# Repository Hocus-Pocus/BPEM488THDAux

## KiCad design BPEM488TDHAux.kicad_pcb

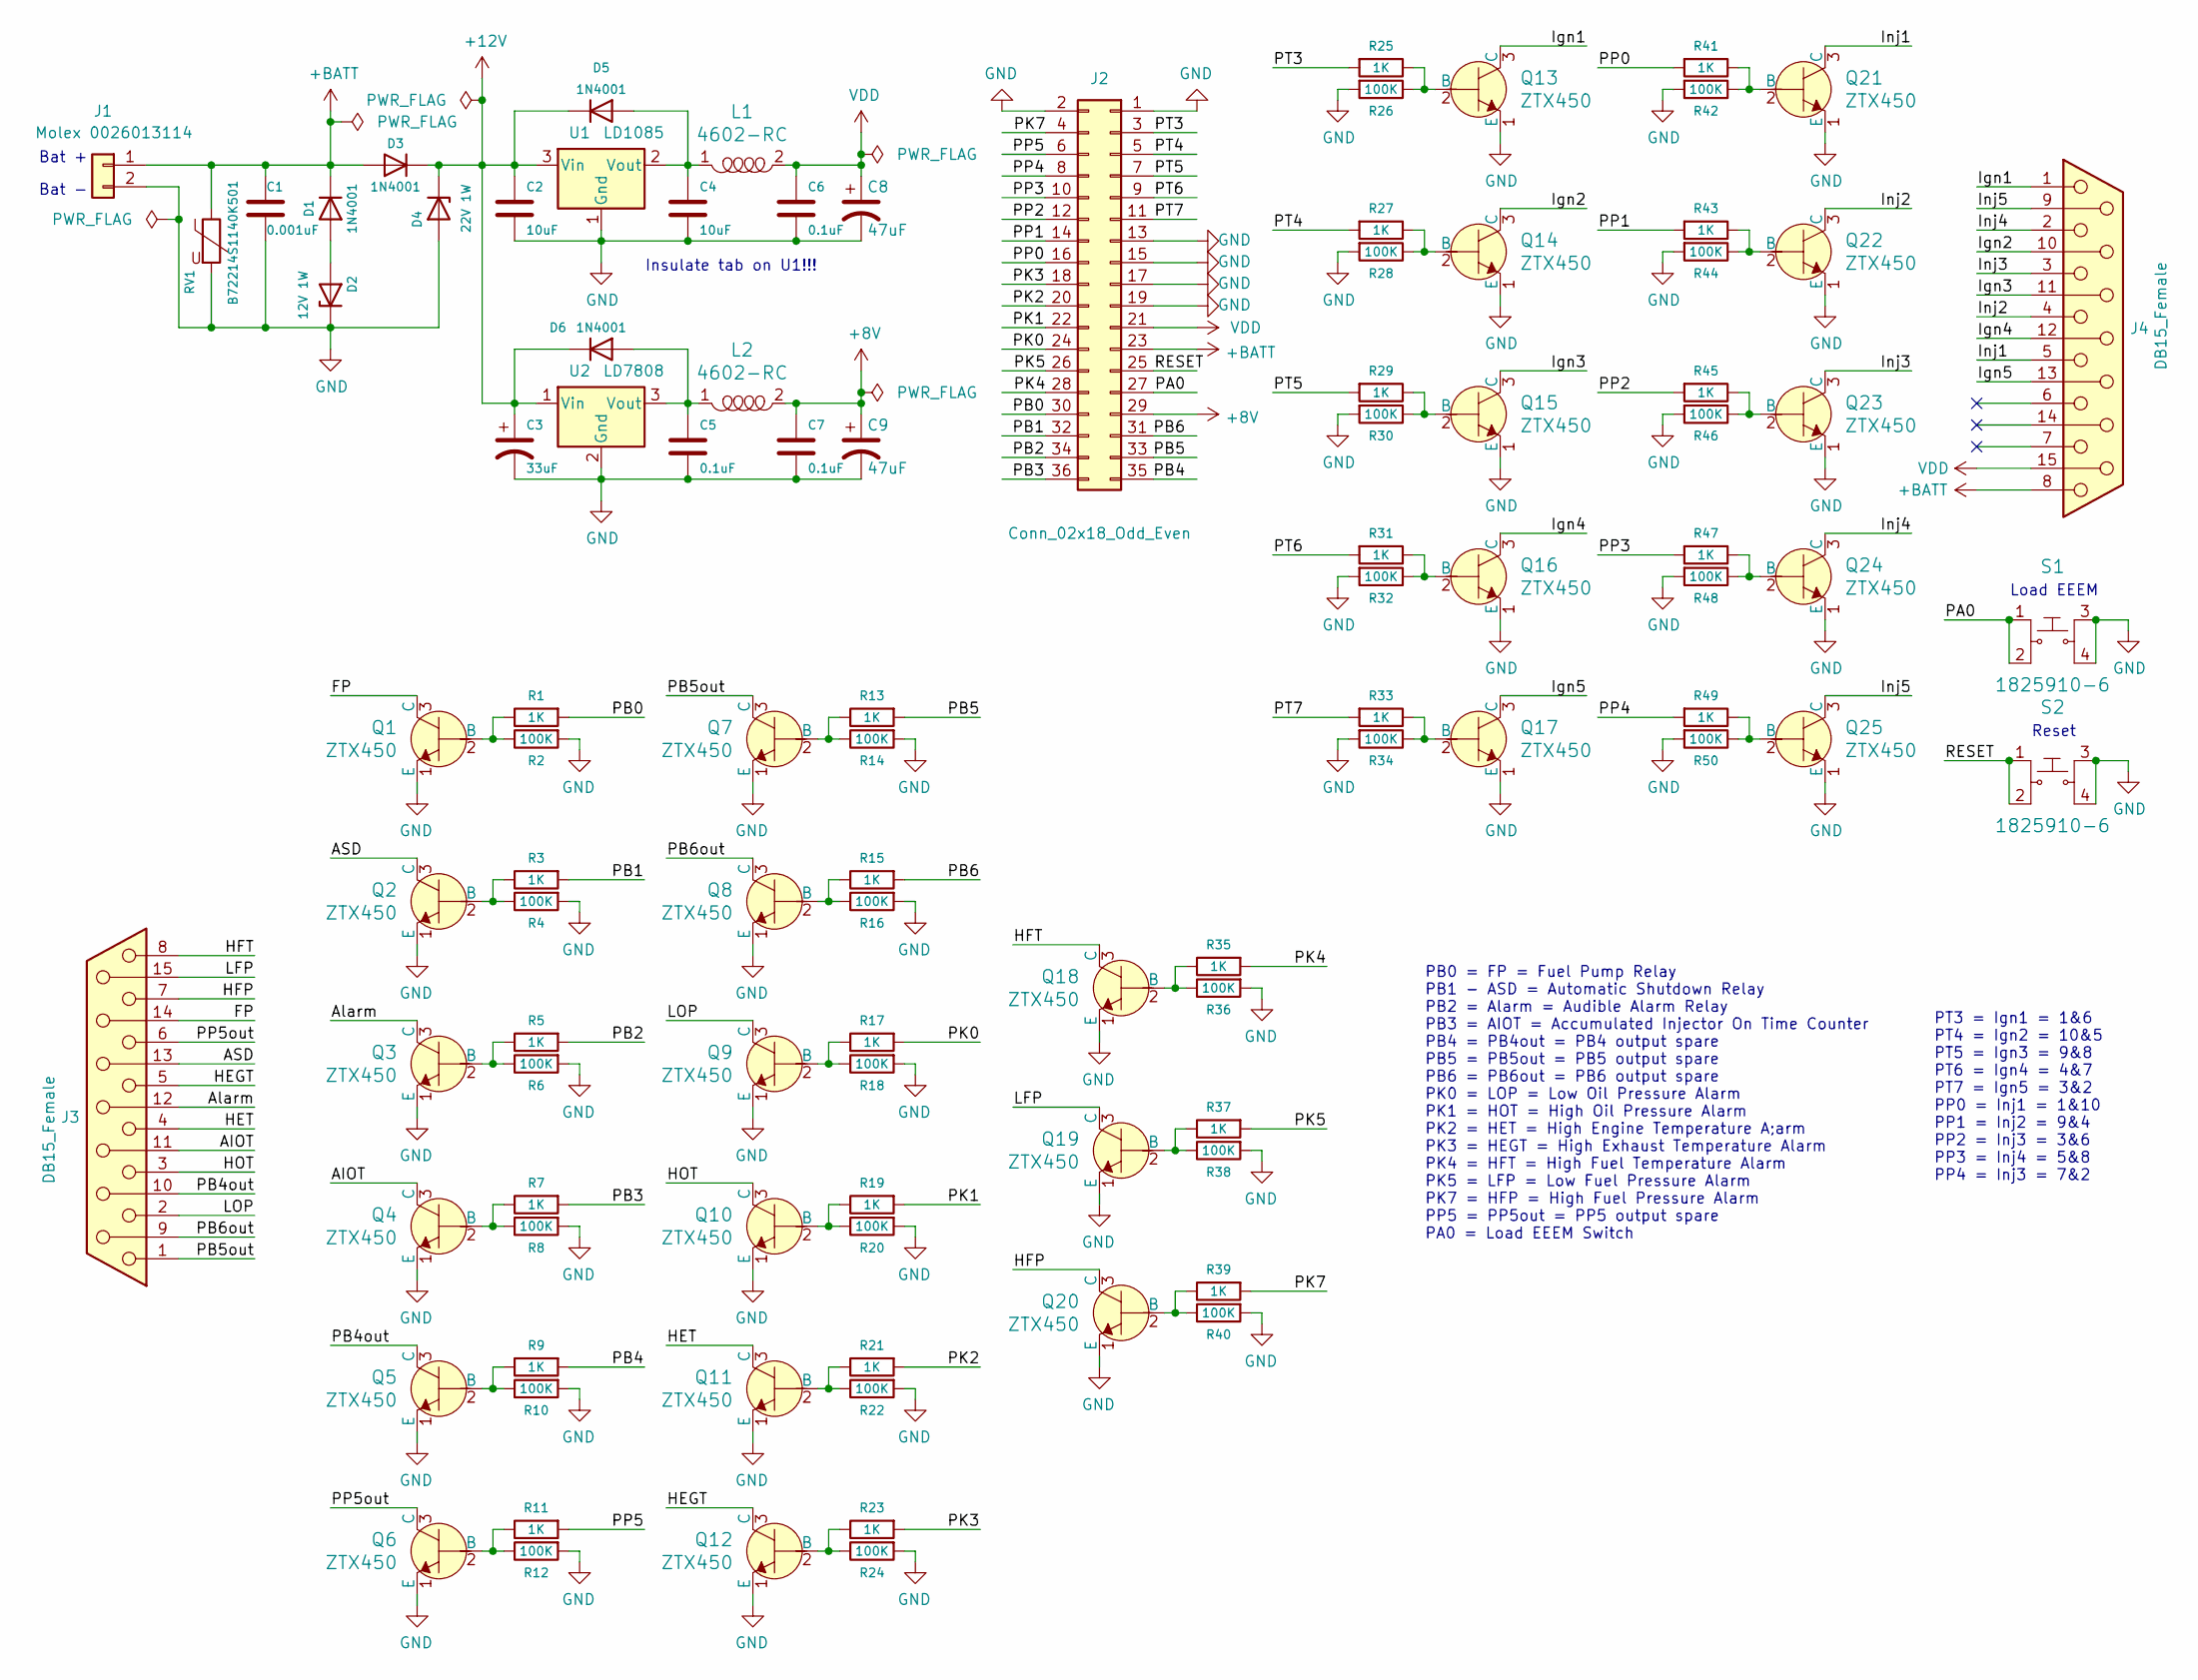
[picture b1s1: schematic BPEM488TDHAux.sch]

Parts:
C1: 0.001uF; C_Disc_D3.8mm_W2.6mm_P2.50mm; Digikey 399-13913-2-ND
C2, C4: 10uF; C_Disc_D5.0mm_W2.5mm_P2.50mm; Digikey 399-13950-ND
C3: 33uF; CP_Radial_Tantal_D8.0mm_P5.00mm; Digikey 399-3591-ND
C5, C6, C7: 0.1uF; C_Disc_D5.0mm_W2.5mm_P2.50mm; Digikey 399-4264-ND
C8, C9: 47uF; CP_Radial_Tantal_D8.0mm_P5.00mm; Digikey 399-3596-ND
D1, D3, D5, D6: 1N4001; D_DO-41_SOD81_P7.62mm_Horizontal; Digikey 1N4001DICT-ND
D2: 12V 1W; D_DO-41_SOD81_P7.62mm_Horizontal; Digikey 1727-3635-2-ND
D4: 22V 1W; D_DO-41_SOD81_P7.62mm_Horizontal; Digikey MAZ222000GTR-ND
J1: Molex 0026013114; Molex_Mini-Fit_Jr_5569-02A2_2x01_P4.20mm_Horizontal; Digikey WM14505-ND
J2: Conn_02x18_Odd_Even; PinSocket_2x18_P2.54mm_Vertical
J3, J4: DB15_Female; DSUB-15_Female_Horizontal_P2.77x2.84mm_EdgePinOffset7.70mm_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; Digikey A32123-ND
L1, L2: 4602-RC; L_Axial_L16.0mm_D6.3mm_P25.40mm_Horizontal_Fastron_VHBCC; Digikey 4602-RC-ND
Q1, Q2, Q3, Q4, Q5, Q6, Q7, Q8, Q9, Q10, Q11, Q12, Q13, Q14, Q15, Q16, Q17, Q18, Q19, Q20, Q21, Q22, Q23, Q24, Q25: ZTX450; TO-92-3; MPN ZTX450; Digi-Key_PN ZTX450-ND
R1, R3, R5, R7, R9, R11, R13, R15, R17, R19, R21, R23, R25, R27, R29, R31, R33, R35, R37, R39, R41, R43, R45, R47, R49: 1K; R_Axial_DIN0207_L6.3mm_D2.5mm_P10.16mm_Horizontal; Digikey 1.00KXBK-ND
R2, R4, R6, R8, R10, R12, R14, R16, R18, R20, R22, R24, R26, R28, R30, R32, R34, R36, R38, R40, R42, R44, R46, R48, R50: 100K; R_Axial_DIN0207_L6.3mm_D2.5mm_P10.16mm_Horizontal; Digikey 100KXBK-ND
RV1: B72214S1140K501; RV_Disc_D15.5mm_W3.9mm_P7.5mm; Digikey 495-2057-ND
S1, S2: 1825910-6; Switch_Tactile_THT_6x6mm; MPN 1825910-6; Digi-Key_PN 450-1650-ND
U1: LD1085; TO-220F-3_Horizontal_TabDown; Digikey 497-3436-5-ND
U2: LD7808; TO-220F-3_Horizontal_TabDown; Digike 497-1446-5-ND

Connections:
+8V: C7.1, C9.1, J2.29, L2.2
+12V: C2.1, C3.1, D3.1 (K), D4.1 (K), D5.1 (K), D6.1 (K), U1.3 (Vin), U2.1 (Vin)
+BATT: C1.1, D1.1 (K), D3.2 (A), J1.1, J2.23, J4.8, RV1.1
/AIOT: J3.11 (P111), Q4.3 (C)
/ASD: J3.13, Q2.3 (C)
/Alarm: J3.12, Q3.3 (C)
/FP: J3.14, Q1.3 (C)
/HEGT: J3.5, Q12.3 (C)
/HET: J3.4, Q11.3 (C)
/HFP: J3.7, Q20.3 (C)
/HFT: J3.8, Q18.3 (C)
/HOT: J3.3, Q10.3 (C)
/Ign1: J4.1, Q13.3 (C)
/Ign2: J4.10, Q14.3 (C)
/Ign3: J4.11 (P111), Q15.3 (C)
/Ign4: J4.12, Q16.3 (C)
/Ign5: J4.13, Q17.3 (C)
/Inj1: J4.5, Q21.3 (C)
/Inj2: J4.4, Q22.3 (C)
/Inj3: J4.3, Q23.3 (C)
/Inj4: J4.2, Q24.3 (C)
/Inj5: J4.9, Q25.3 (C)
/LFP: J3.15, Q19.3 (C)
/LOP: J3.2, Q9.3 (C)
/PA0: J2.27, S1.1, S1.2
/PB0: J2.30, R1.2
/PB1: J2.32, R3.2
/PB2: J2.34, R5.2
/PB3: J2.36, R7.2
/PB4: J2.35, R9.2
/PB4out: J3.10, Q5.3 (C)
/PB5: J2.33, R13.2
/PB5out: J3.1, Q7.3 (C)
/PB6: J2.31, R15.2
/PB6out: J3.9, Q8.3 (C)
/PK0: J2.24, R17.2
/PK1: J2.22, R19.2
/PK2: J2.20, R21.2
/PK3: J2.18, R23.2
/PK4: J2.28, R35.2
/PK5: J2.26, R37.2
/PK7: J2.4, R39.2
/PP0: J2.16, R41.2
/PP1: J2.14, R43.2
/PP2: J2.12, R45.2
/PP3: J2.10, R47.2
/PP4: J2.8, R49.2
/PP5: J2.6, R11.2
/PP5out: J3.6, Q6.3 (C)
/PT3: J2.3, R25.2
/PT4: J2.5, R27.2
/PT5: J2.7, R29.2
/PT6: J2.9, R31.2
/PT7: J2.11, R33.2
/RESET: J2.25, S2.1, S2.2
GND: C1.2, C2.2, C3.2, C4.2, C5.2, C6.2, C7.2, C8.2, C9.2, D2.1 (K), D4.2 (A), J1.2, J2.1, J2.2, J2.13, J2.15, J2.17, J2.19, Q1.1 (E), Q2.1 (E), Q3.1 (E), Q4.1 (E), Q5.1 (E), Q6.1 (E), Q7.1 (E), Q8.1 (E), Q9.1 (E), Q10.1 (E), Q11.1 (E), Q12.1 (E), Q13.1 (E), Q14.1 (E), Q15.1 (E), Q16.1 (E), Q17.1 (E), Q18.1 (E), Q19.1 (E), Q20.1 (E), Q21.1 (E), Q22.1 (E), Q23.1 (E), Q24.1 (E), Q25.1 (E), R2.2, R4.2, R6.2, R8.2, R10.2, R12.2, R14.2, R16.2, R18.2, R20.2, R22.2, R24.2, R26.2, R28.2, R30.2, R32.2, R34.2, R36.2, R38.2, R40.2, R42.2, R44.2, R46.2, R48.2, R50.2, RV1.2, S1.3, S1.4, S2.3, S2.4, U1.1 (Gnd), U2.2 (Gnd)
unnamed: C4.1, D5.2 (A), L1.1, U1.2 (Vout)
unnamed: C5.1, D6.2 (A), L2.1, U2.3 (Vout)
unnamed: D1.2 (A), D2.2 (A)
unnamed: Q1.2 (B), R1.1, R2.1
unnamed: Q2.2 (B), R3.1, R4.1
unnamed: Q3.2 (B), R5.1, R6.1
unnamed: Q4.2 (B), R7.1, R8.1
unnamed: Q5.2 (B), R9.1, R10.1
unnamed: Q6.2 (B), R11.1, R12.1
unnamed: Q7.2 (B), R13.1, R14.1
unnamed: Q8.2 (B), R15.1, R16.1
unnamed: Q9.2 (B), R17.1, R18.1
unnamed: Q10.2 (B), R19.1, R20.1
unnamed: Q11.2 (B), R21.1, R22.1
unnamed: Q12.2 (B), R23.1, R24.1
unnamed: Q13.2 (B), R25.1, R26.1
unnamed: Q14.2 (B), R27.1, R28.1
unnamed: Q15.2 (B), R29.1, R30.1
unnamed: Q16.2 (B), R31.1, R32.1
unnamed: Q17.2 (B), R33.1, R34.1
unnamed: Q18.2 (B), R35.1, R36.1
unnamed: Q19.2 (B), R37.1, R38.1
unnamed: Q20.2 (B), R39.1, R40.1
unnamed: Q21.2 (B), R41.1, R42.1
unnamed: Q22.2 (B), R43.1, R44.1
unnamed: Q23.2 (B), R45.1, R46.1
unnamed: Q24.2 (B), R47.1, R48.1
unnamed: Q25.2 (B), R49.1, R50.1
VDD: C6.1, C8.1, J2.21, J4.15, L1.2

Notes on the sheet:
Load EEEM
Reset
Bat -
Bat +
PB0 = FP = Fuel Pump Relay PB1 - ASD = Automatic Shutdown Relay PB2 = Alarm = Audible Alarm Relay PB3 = AIOT = Accumulated Injector On Time Counter PB4 = PB4out = PB4 output spare PB5 = PB5out = PB5 output spare PB6 = PB6out = PB6 output spare PK0 = LOP = Low Oil Pressure Alarm PK1 = HOT = High Oil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
PT3 = Ign1 = 1&6 PT4 = Ign2 = 10&5 PT5 = Ign3 = 9&8 PT6 = Ign4 = 4&7 PT7 = Ign5 = 3&2 PP0 = Inj1 = 1&10 PP1 = Inj2 = 9&4 PP2 = Inj3 = 3&6 PP3 = Inj4 = 5&8 PP4 = Inj3 = 7&2
Insulate tab on U1!!!

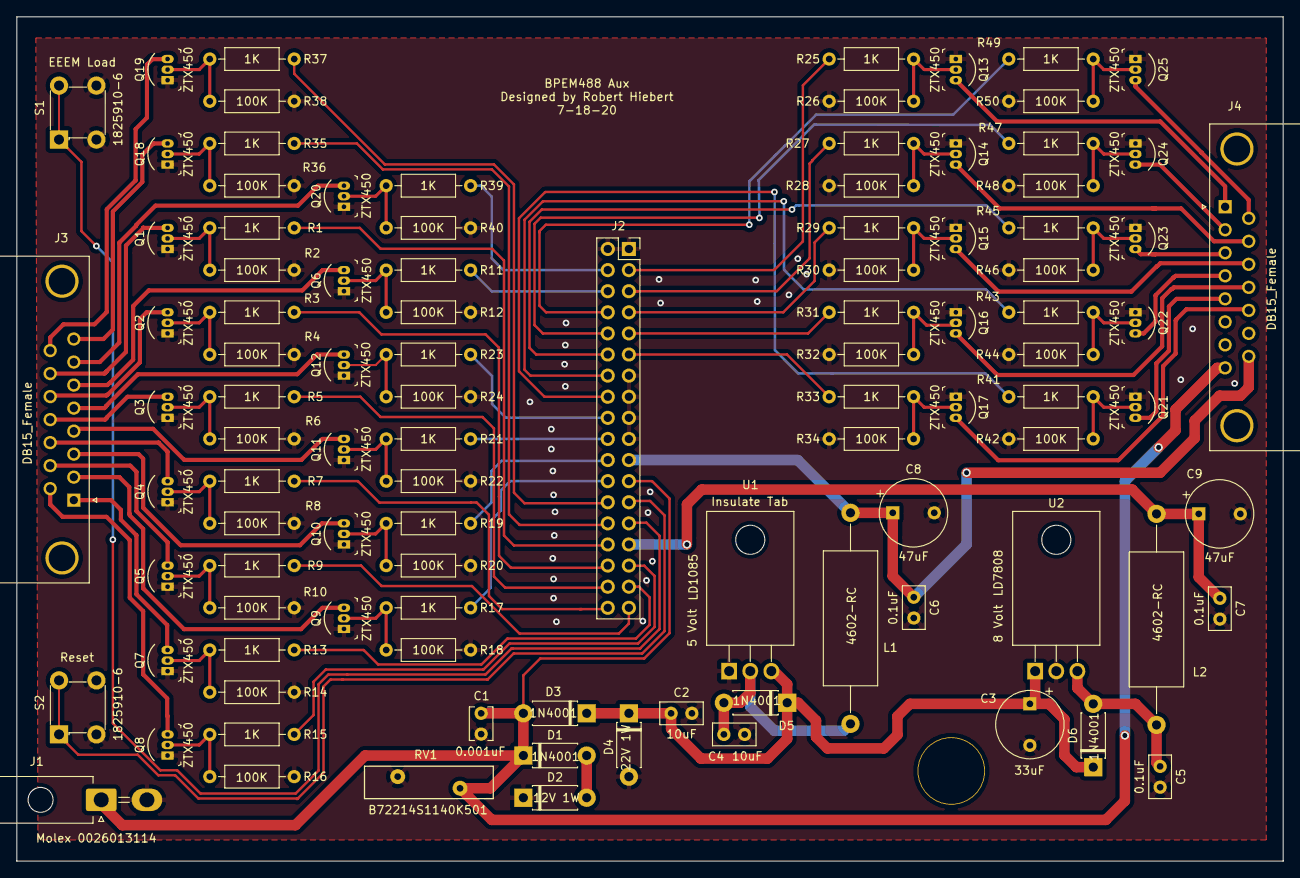
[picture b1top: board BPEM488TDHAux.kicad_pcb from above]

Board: 2 copper layers, 152.4 x 101.6 mm, 101 parts (0 on the bottom side), 85 nets.

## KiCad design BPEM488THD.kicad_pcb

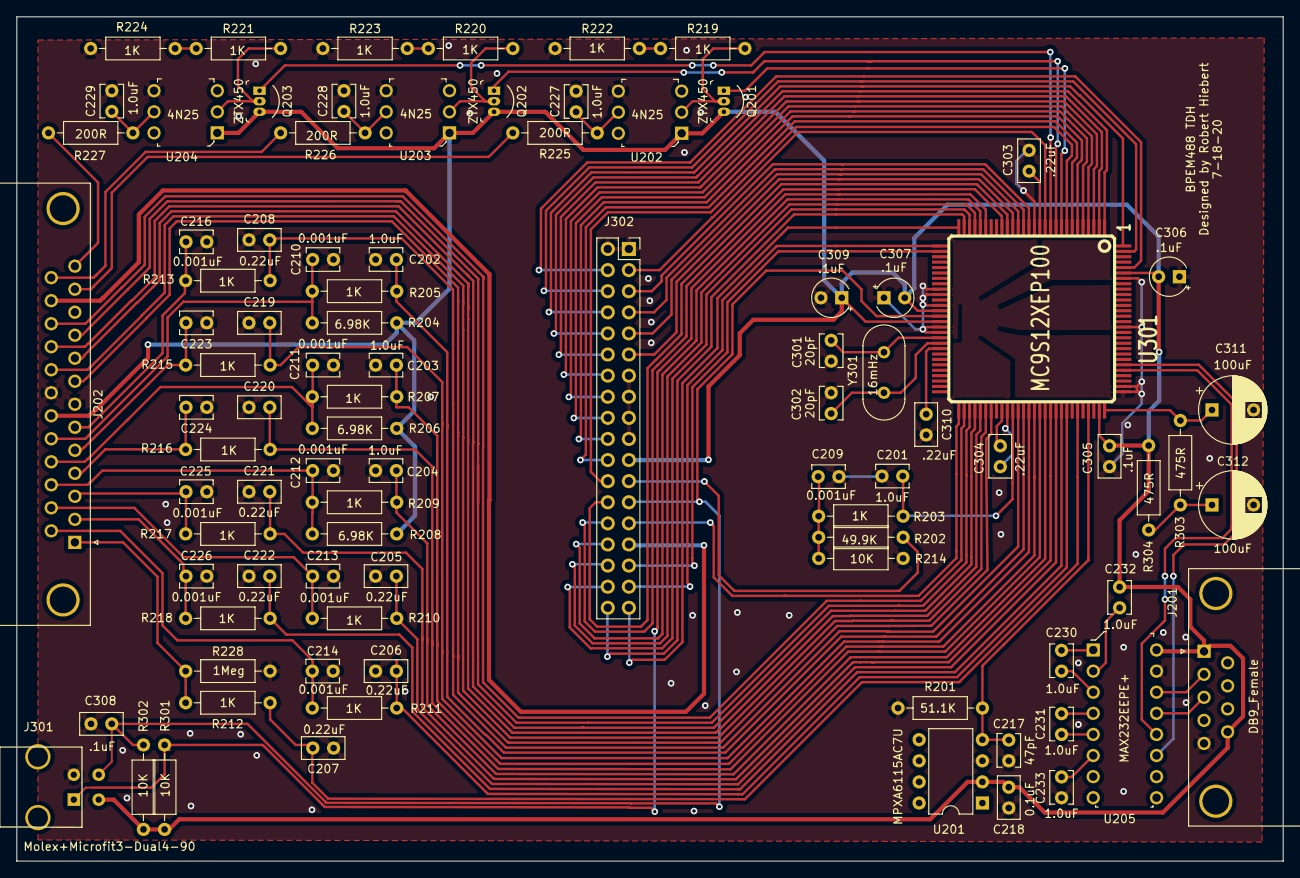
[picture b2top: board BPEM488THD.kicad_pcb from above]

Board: 2 copper layers, 152.4 x 101.6 mm, 90 parts (0 on the bottom side), 95 nets.

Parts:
C201, C202, C203, C204, C227, C228, C229, C230, C231, C232, C233: 1.0uF; C_Disc_D3.8mm_W2.6mm_P2.50mm
C205, C206, C207, C208, C219, C220, C221, C222: 0.22uF; C_Disc_D5.0mm_W2.5mm_P2.50mm
C209, C210, C211, C212, C213, C214, C216, C223, C224, C225, C226: 0.001uF; C_Disc_D3.8mm_W2.6mm_P2.50mm
C217: 47pF; C_Disc_D3.8mm_W2.6mm_P2.50mm
C218: 0.1uF; C_Disc_D5.0mm_W2.5mm_P2.50mm
C301, C302: 20pF; C_Disc_D3.8mm_W2.6mm_P2.50mm
C303, C304, C310: .22uF; C_Disc_D5.0mm_W2.5mm_P2.50mm
C305, C308: .1uF; C_Disc_D5.0mm_W2.5mm_P2.50mm
C306, C307, C309: .1uF; CP_Radial_Tantal_D4.5mm_P2.50mm
C311, C312: 100uF; CP_Radial_D8.0mm_P5.00mm
J201: DB9_Female; DSUB-9_Female_Horizontal_P2.77x2.84mm_EdgePinOffset9.90mm_H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
J202: DB25_Female; DSUB-25_Female_Horizontal_P2.77x2.84mm_EdgePinOffset7.70mm_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
J301: Molex+Microfit3-Dual4-90; Molex-Microfit3-Dual4-90
J302: Conn_02x18_Odd_Even; PinSocket_2x18_P2.54mm_Vertical
Q201, Q202, Q203: ZTX450; TO-92-3
R201: 51.1K; R_Axial_DIN0207_L6.3mm_D2.5mm_P10.16mm_Horizontal
R202: 49.9K; R_Axial_DIN0207_L6.3mm_D2.5mm_P10.16mm_Horizontal
R203, R205, R207, R209, R210, R211, R212, R213, R215, R216, R217, R218, R219, R220, R221, R222, R223, R224: 1K; R_Axial_DIN0207_L6.3mm_D2.5mm_P10.16mm_Horizontal
R204, R206, R208: 6.98K; R_Axial_DIN0207_L6.3mm_D2.5mm_P10.16mm_Horizontal
R214, R301, R302: 10K; R_Axial_DIN0207_L6.3mm_D2.5mm_P10.16mm_Horizontal
R225, R226, R227: 200R; R_Axial_DIN0207_L6.3mm_D2.5mm_P10.16mm_Horizontal
R228: 1Meg; R_Axial_DIN0207_L6.3mm_D2.5mm_P10.16mm_Horizontal
R303, R304: 475R; R_Axial_DIN0207_L6.3mm_D2.5mm_P10.16mm_Horizontal
U201: MPXA6115AC7U; DIP-8_W7.62mm
U202, U203, U204: 4N25; DIP-6_W7.62mm
U205: MAX232EEPE+; DIP-16_W7.62mm
U301: MC9S12XEP100; PQFP112
Y301: 16mHz; Crystal_HC49-4H_Vertical

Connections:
+8V: J202.24, J302.29
+BATT: J302.23, R202.2
/CPU/PA0: J302.27, U301.57
/CPU/PB0: J302.30, U301.24
/CPU/PB1: J302.32, U301.25
/CPU/PB2: J302.34, U301.26
/CPU/PB3: J302.36, U301.27
/CPU/PB4: J302.35, U301.28
/CPU/PB5: J302.33, U301.29
/CPU/PB6: J302.31, U301.30
/CPU/PK0: J302.24, U301.8
/CPU/PK1: J302.22, U301.7
/CPU/PK2: J302.20, U301.6
/CPU/PK3: J302.18, U301.5
/CPU/PK4: J302.28, U301.20
/CPU/PK5: J302.26, U301.19
/CPU/PK7: J302.4, U301.108
/CPU/PP0: J302.16, U301.4
/CPU/PP1: J302.14, U301.3
/CPU/PP2: J302.12, U301.2
/CPU/PP3: J302.10, U301.1
/CPU/PP4: J302.8, U301.112
/CPU/PP5: J302.6, U301.111
/CPU/PT3: J302.3, U301.12
/CPU/PT4: J302.5, U301.15
/CPU/PT5: J302.7, U301.16
/CPU/PT6: J302.9, U301.17
/CPU/PT7: J302.11, U301.18
/CPU/RESET: C308.1, J301.4, J302.25, R302.2, U301.42
/Inputs_RS232/CKP: J202.25, R226.1
/Inputs_RS232/CLT: C210.2, J202.18, R204.1, R205.1
/Inputs_RS232/CMP: J202.12, R225.1
/Inputs_RS232/EFP: C223.2, J202.5, R215.1
/Inputs_RS232/EGO: J202.1, R212.1, R228.1
/Inputs_RS232/EOP: C216.2, J202.6, R213.1
/Inputs_RS232/Ftrm: C225.2, J202.3, R217.1
/Inputs_RS232/Itrm: C224.2, J202.4, R216.1
/Inputs_RS232/MAP: C213.2, J202.15, R210.1
/Inputs_RS232/MAT: C211.2, J202.17, R206.1, R207.1
/Inputs_RS232/PAD03in: C212.2, J202.16, R208.1, R209.1
/Inputs_RS232/PAD12in: C226.2, J202.2, R218.1
/Inputs_RS232/TPS: C214.2, J202.14, R211.1
/Inputs_RS232/VSPD: J202.13, R227.1
GND: C201.1, C202.1, C203.1, C204.1, C205.1, C206.1, C207.1, C208.1, C209.1, C210.1, C211.1, C212.1, C213.1, C214.1, C216.1, C217.1, C218.2, C219.1, C220.1, C221.1, C222.1, C223.1, C224.1, C225.1, C226.1, C227.1, C228.1, C229.1, C233.1, C301.1, C302.1, C303.1, C304.1, C305.1, C306.1, C307.1, C308.2, C309.2, C310.2, C311.2, C312.2, J201.5, J202.7, J202.11, J202.20, J301.2, J302.1, J302.2, J302.13, J302.15, J302.17, J302.19, R201.2, R214.1, R222.1, R223.1, R224.1, R228.2, U201.3, U202.4, U203.4, U204.4, U205.15, U301.14, U301.37, U301.38, U301.40, U301.44, U301.45, U301.66, U301.85, U301.86, U301.97, U301.106
unnamed: C209.2, R202.1, R203.1, R214.2
unnamed: C227.2, R225.2, U202.5
unnamed: C228.2, R226.2, U203.5
unnamed: C229.2, R227.2, U204.5
unnamed: C230.1, U205.3
unnamed: C230.2, U205.1
unnamed: C231.1, U205.5
unnamed: C231.2, U205.4
unnamed: C232.1, U205.2
unnamed: C233.2, U205.6
unnamed: C301.2, U301.46, Y301.2
unnamed: C302.2, U301.47, Y301.1
unnamed: C303.2, U301.13
unnamed: C304.2, U301.65
unnamed: C310.1, U301.48
unnamed: C311.1, R303.1, U301.84
unnamed: C312.1, R303.2, R304.1
unnamed: J201.2, U205.14
unnamed: J201.3, U205.13
unnamed: J301.1, R301.2, U301.23
unnamed: Q201.2, R219.2, U202.2
unnamed: Q202.2, R220.2, U203.2
unnamed: Q203.2, R221.2, U204.2
unnamed: R219.1, R222.2
unnamed: R220.1, R223.2
unnamed: R221.1, R224.2
PA1: J202.23, U301.58
PA2: J202.10, U301.59
PA3: J202.22, U301.60
PA4: J202.9, U301.61
PA5: J202.21, U301.62
PA6: J202.8, U301.63
PAD00: C201.2, R203.2, U301.67
PAD01: C202.2, R205.2, U301.69
PAD02: C203.2, R207.2, U301.71
PAD03: C204.2, R209.2, U301.73
PAD04: C205.2, R210.2, U301.75
PAD05: C206.2, R211.2, U301.77
PAD06: C207.2, R212.2, U301.79
PAD07: C217.2, R201.1, U201.4, U301.81
PAD08: C208.2, R213.2, U301.68
PAD09: C219.2, R215.2, U301.70
PAD10: C220.2, R216.2, U301.72
PAD11: C221.2, R217.2, U301.74
PAD12: C222.2, R218.2, U301.76
PS0: U205.12, U301.89
PS1: U205.11, U301.90
PT0: Q201.1, U301.9
PT1: Q202.1, U301.10
PT2: Q203.1, U301.11
VDD: C218.1, C232.2, C305.2, C306.2, C307.2, C309.1, J201.1, J201.9, J202.19, J301.3, J302.21, Q201.3, Q202.3, Q203.3, R204.2, R206.2, R208.2, R301.1, R302.1, R304.2, U201.2, U202.1, U203.1, U204.1, U205.16, U301.41, U301.43, U301.83, U301.107
